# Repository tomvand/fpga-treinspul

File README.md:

# Docker

```bash
xhost +local:docker
docker compose up --build
```

Inside the container:

```console
cd /workspace

# Launch Icestudio
icestudio

# Launch KiCad
kicad
```

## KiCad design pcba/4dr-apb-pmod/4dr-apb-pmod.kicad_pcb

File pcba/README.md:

PCBA designs and gerbers go here.

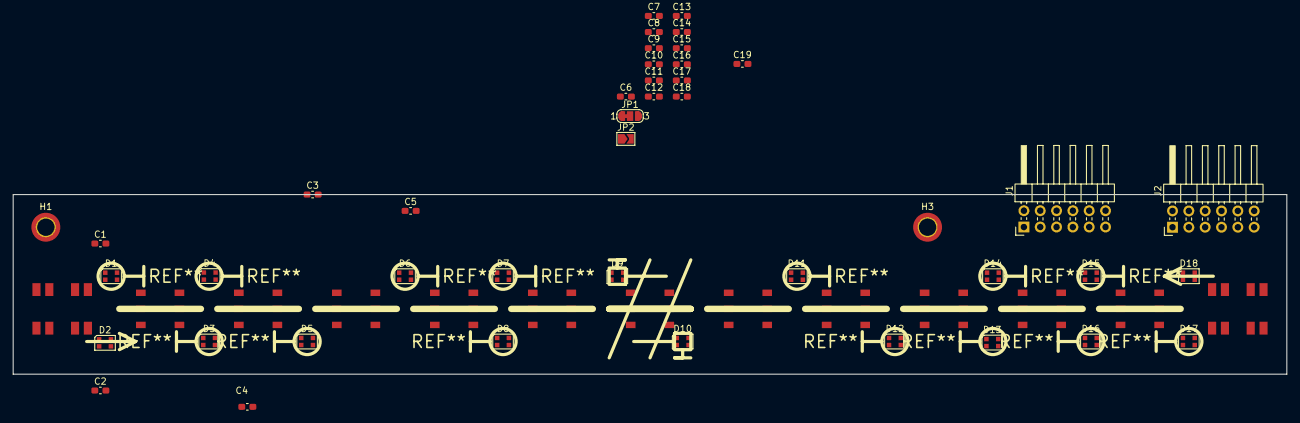
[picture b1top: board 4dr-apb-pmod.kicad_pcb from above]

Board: 2 copper layers, 198.1 x 27.9 mm, 45 parts (0 on the bottom side), 6 nets, no tracks yet.

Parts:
C1, C2, C3, C4, C5, C6, C7, C8, C9, C10, C11, C12, C13, C14, C15, C16, C17, C18, C19: 0.1u; C_0603_1608Metric_Pad1.08x0.95mm_HandSolder
D1, D2, D3, D4, D5, D6, D7, D8, D9, D10, D11, D12, D13, D14, D15, D16, D17, D18: WS2812B-2020; LED_WS2812B-2020_PLCC4_2.0x2.0mm
Deboard-model1: MountingHole_Pad; icebreaker_dev
H1, H3: MountingHole_Pad; MountingHole_2.7mm_M2.5_ISO7380_Pad_TopOnly
H2: MountingHole_Pad; icebreaker_dev
J1, J2: Conn_02x06_Row_Letter_Last; PinHeader_2x06_P2.54mm_Horizontal
JP1: SolderJumper_3_Bridged12; SolderJumper-3_P1.3mm_Bridged12_RoundedPad1.0x1.5mm_NumberL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
JP2: SolderJumper_2_Open; SolderJumper-2_P1.3mm_Open_TrianglePad1.0x1.5mm

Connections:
unnamed: C19.2, D1.4 (VDD), D2.4 (VDD), D3.4 (VDD), D4.4 (VDD)
unnamed: C19.1, D1.2 (VSS)
unnamed: C1.2, D5.4 (VDD), D6.4 (VDD), D7.4 (VDD), D8.4 (VDD)
unnamed: C1.1, D5.2 (VSS), D6.2 (VSS), D7.2 (VSS), D8.2 (VSS)
unnamed: C8.2, D9.4 (VDD), D10.4 (VDD), D11.4 (VDD), D12.4 (VDD)
unnamed: D13.4 (VDD), D14.4 (VDD), D15.4 (VDD)

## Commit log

2026-01-10 4dr-apb pcba graphical design
2026-01-10 Add addressable led icestudio experiment
2026-01-10 [WIP] Add dockerized dev environment
2026-01-11 Add vscode devcontainer
2026-01-23 Add schematic and 3D models
